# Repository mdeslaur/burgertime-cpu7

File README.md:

# Burgertime CPU-7 module

This is a 1-for-1 reproduction of the Burgertime CPU-7 module which came
encapsulated in epoxy.

The layout and routing is as close to original as possible.

The original board has a wire running from pin 10 of IC3 to a pad on the
lower right corner, and then to the ground plane of the main PCB stack. This
reproduction may work without it, but it is best to add it like on the
original.

Pictures of the original board and a PDF schematic are available in the
docs directory. The gerbers for JLCPCB are in the zip file in the gerbers
directory.

Change history:  
1.0 - Initial version  
1.1 - Updated to add component values, gerbers, and docs.  

To Do:  

Marc Deslauriers  
2022-08-04

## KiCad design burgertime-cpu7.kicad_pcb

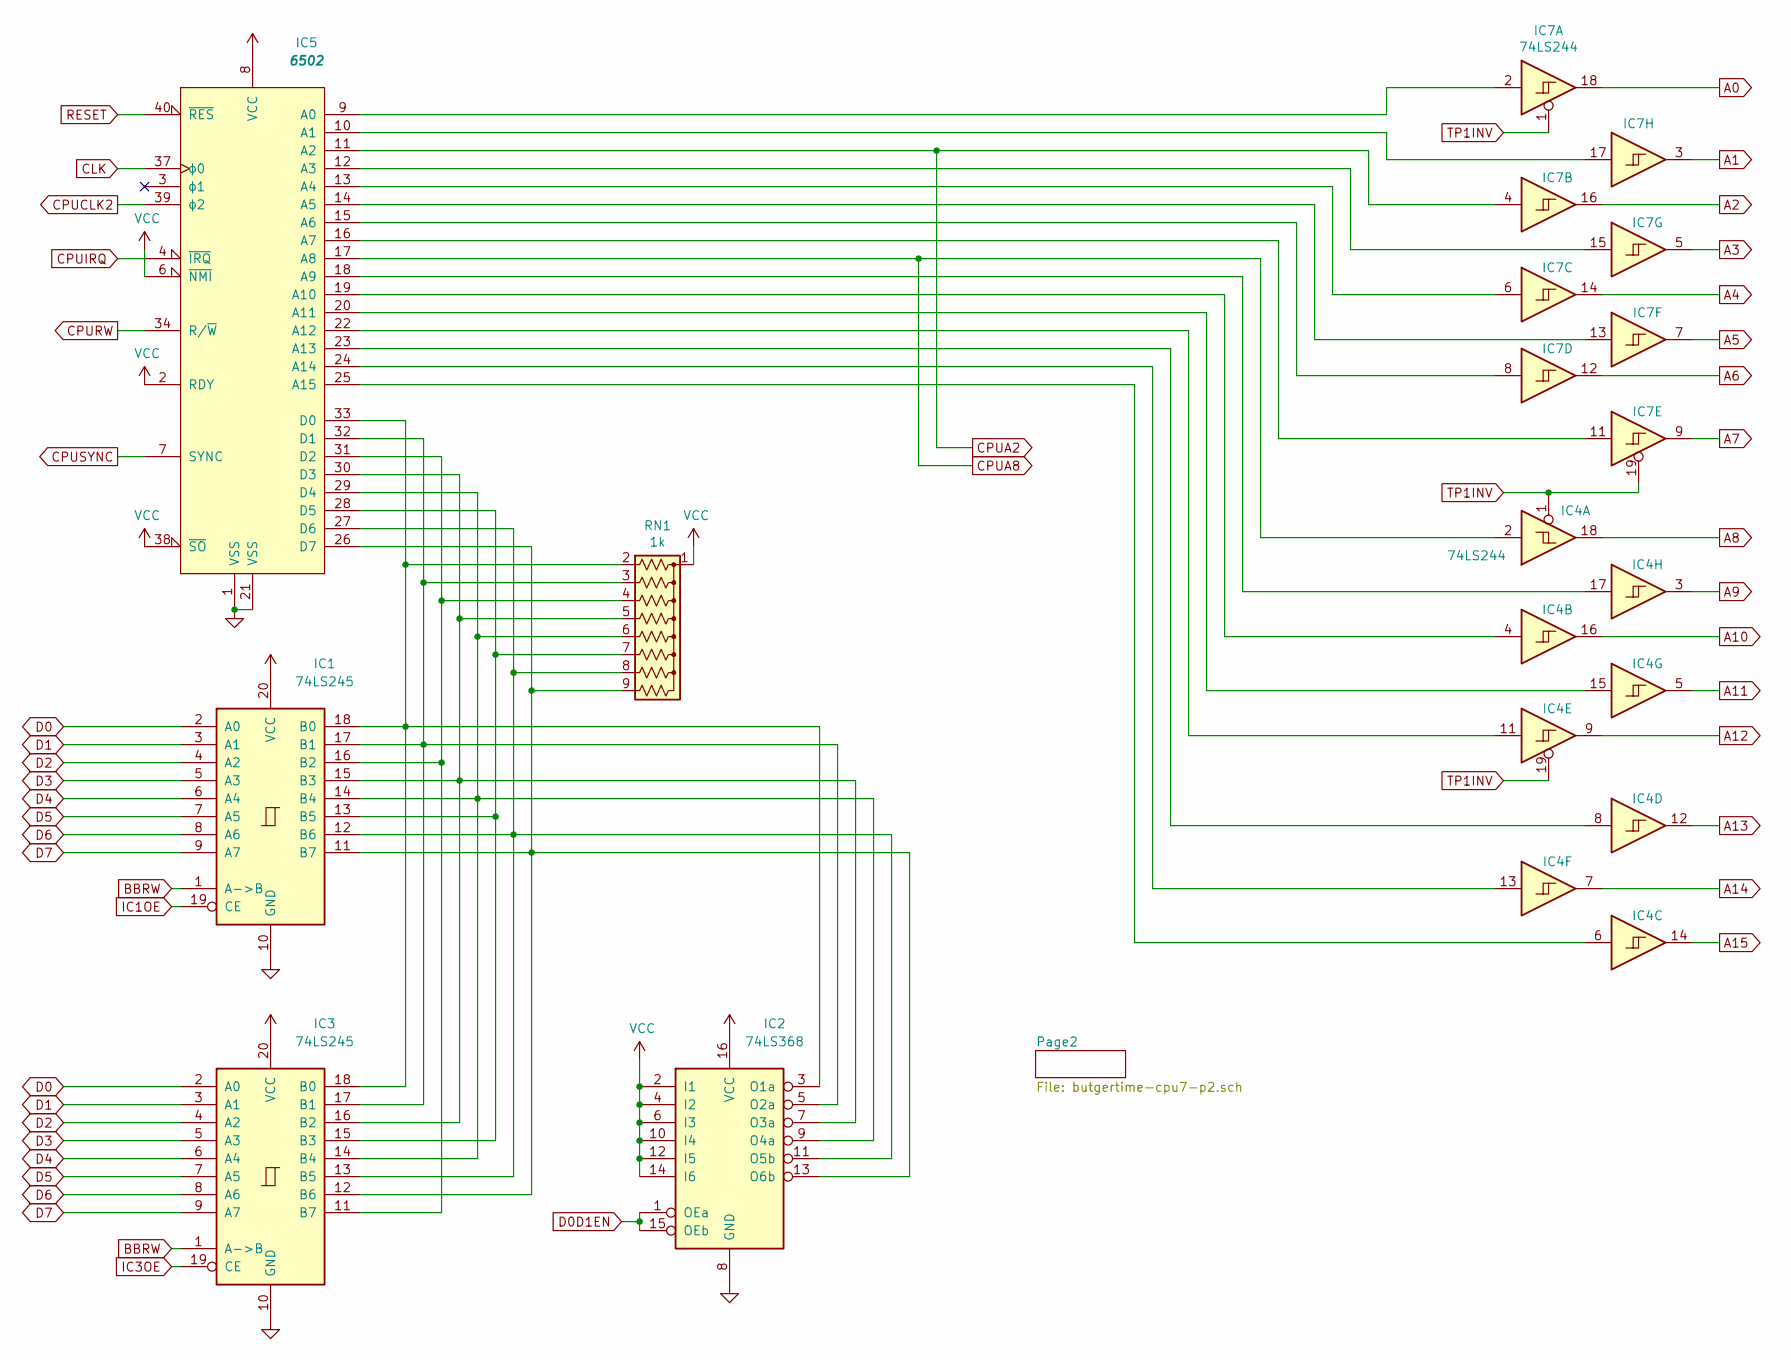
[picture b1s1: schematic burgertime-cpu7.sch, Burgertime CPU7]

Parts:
IC1, IC3: 74LS245; DIP-20_W7.62mm
IC2: 74LS368; DIP-16_W7.62mm
IC4, IC7: 74LS244; DIP-20_W7.62mm
IC5: 6502; DIP-40_W15.24mm
RN1: 1k; R_Array_SIP9

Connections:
A0: IC7.18; also elsewhere on the board
A1: IC7.3; also elsewhere on the board
A2: IC7.16; also elsewhere on the board
A3: IC7.5; also elsewhere on the board
A4: IC7.14; also elsewhere on the board
A5: IC7.7; also elsewhere on the board
A6: IC7.12; also elsewhere on the board
A7: IC7.9; also elsewhere on the board
A8: IC4.18; also elsewhere on the board
A9: IC4.3; also elsewhere on the board
A10: IC4.16; also elsewhere on the board
A11: IC4.5; also elsewhere on the board
A12: IC4.9; also elsewhere on the board
A13: IC4.12; also elsewhere on the board
A14: IC4.7; also elsewhere on the board
A15: IC4.14; also elsewhere on the board
BBRW: IC1.1 (A->B), IC3.1 (A->B); also elsewhere on the board
CLK: IC5.37 (ϕ0); also elsewhere on the board
CPUA2: IC5.11 (A2), IC7.4; also elsewhere on the board
CPUA8: IC4.2, IC5.17 (A8); also elsewhere on the board
CPUCLK2: IC5.39 (ϕ2); also elsewhere on the board
CPUIRQ: IC5.4 (~IRQ); also elsewhere on the board
CPURW: IC5.34 (R/~W); also elsewhere on the board
CPUSYNC: IC5.7 (SYNC); also elsewhere on the board
D0: IC1.2 (A0), IC3.2 (A0); also elsewhere on the board
D0D1EN: IC2.1 (OEa), IC2.15 (OEb); also elsewhere on the board
D1: IC1.3 (A1), IC3.3 (A1); also elsewhere on the board
D2: IC1.4 (A2), IC3.4 (A2); also elsewhere on the board
D3: IC1.5 (A3), IC3.5 (A3); also elsewhere on the board
D4: IC1.6 (A4), IC3.6 (A4); also elsewhere on the board
D5: IC1.7 (A5), IC3.7 (A5); also elsewhere on the board
D6: IC1.8 (A6), IC3.8 (A6); also elsewhere on the board
D7: IC1.9 (A7), IC3.9 (A7); also elsewhere on the board
GND: IC1.10 (GND), IC2.8 (GND), IC3.10 (GND), IC5.1 (VSS), IC5.21 (VSS); also elsewhere on the board
IC1OE: IC1.19 (CE); also elsewhere on the board
IC3OE: IC3.19 (CE); also elsewhere on the board
unnamed: IC1.11 (B7), IC2.13 (O6b), IC3.12 (B6), IC5.26 (D7), RN1.9 (R8)
unnamed: IC1.12 (B6), IC2.11 (O5b), IC3.13 (B5), IC5.27 (D6), RN1.8 (R7)
unnamed: IC1.13 (B5), IC3.15 (B3), IC5.28 (D5), RN1.7 (R6)
unnamed: IC1.14 (B4), IC2.9 (O4a), IC3.14 (B4), IC5.29 (D4), RN1.6 (R5)
unnamed: IC1.15 (B3), IC2.7 (O3a), IC3.16 (B2), IC5.30 (D3), RN1.5 (R4)
unnamed: IC1.16 (B2), IC3.11 (B7), IC5.31 (D2), RN1.4 (R3)
unnamed: IC1.17 (B1), IC2.5 (O2a), IC3.17 (B1), IC5.32 (D1), RN1.3 (R2)
unnamed: IC1.18 (B0), IC2.3 (O1a), IC3.18 (B0), IC5.33 (D0), RN1.2 (R1)
unnamed: IC4.4, IC5.19 (A10)
unnamed: IC4.6, IC5.25 (A15)
unnamed: IC4.8, IC5.23 (A13)
unnamed: IC4.11, IC5.22 (A12)
unnamed: IC4.13, IC5.24 (A14)
unnamed: IC4.15, IC5.20 (A11)
unnamed: IC4.17, IC5.18 (A9)
unnamed: IC5.9 (A0), IC7.2
unnamed: IC5.10 (A1), IC7.17
unnamed: IC5.12 (A3), IC7.15
unnamed: IC5.13 (A4), IC7.6
unnamed: IC5.14 (A5), IC7.13
unnamed: IC5.15 (A6), IC7.8
unnamed: IC5.16 (A7), IC7.11
RESET: IC5.40 (~RES); also elsewhere on the board
TP1INV: IC4.1, IC4.19, IC7.1, IC7.19; also elsewhere on the board
VCC: IC1.20 (VCC), IC2.2 (I1), IC2.4 (I2), IC2.6 (I3), IC2.10 (I4), IC2.12 (I5), IC2.14 (I6), IC2.16 (VCC), IC3.20 (VCC), IC5.2 (RDY), IC5.6 (~NMI), IC5.8 (VCC), IC5.38 (~SO), RN1.1 (common); also elsewhere on the board

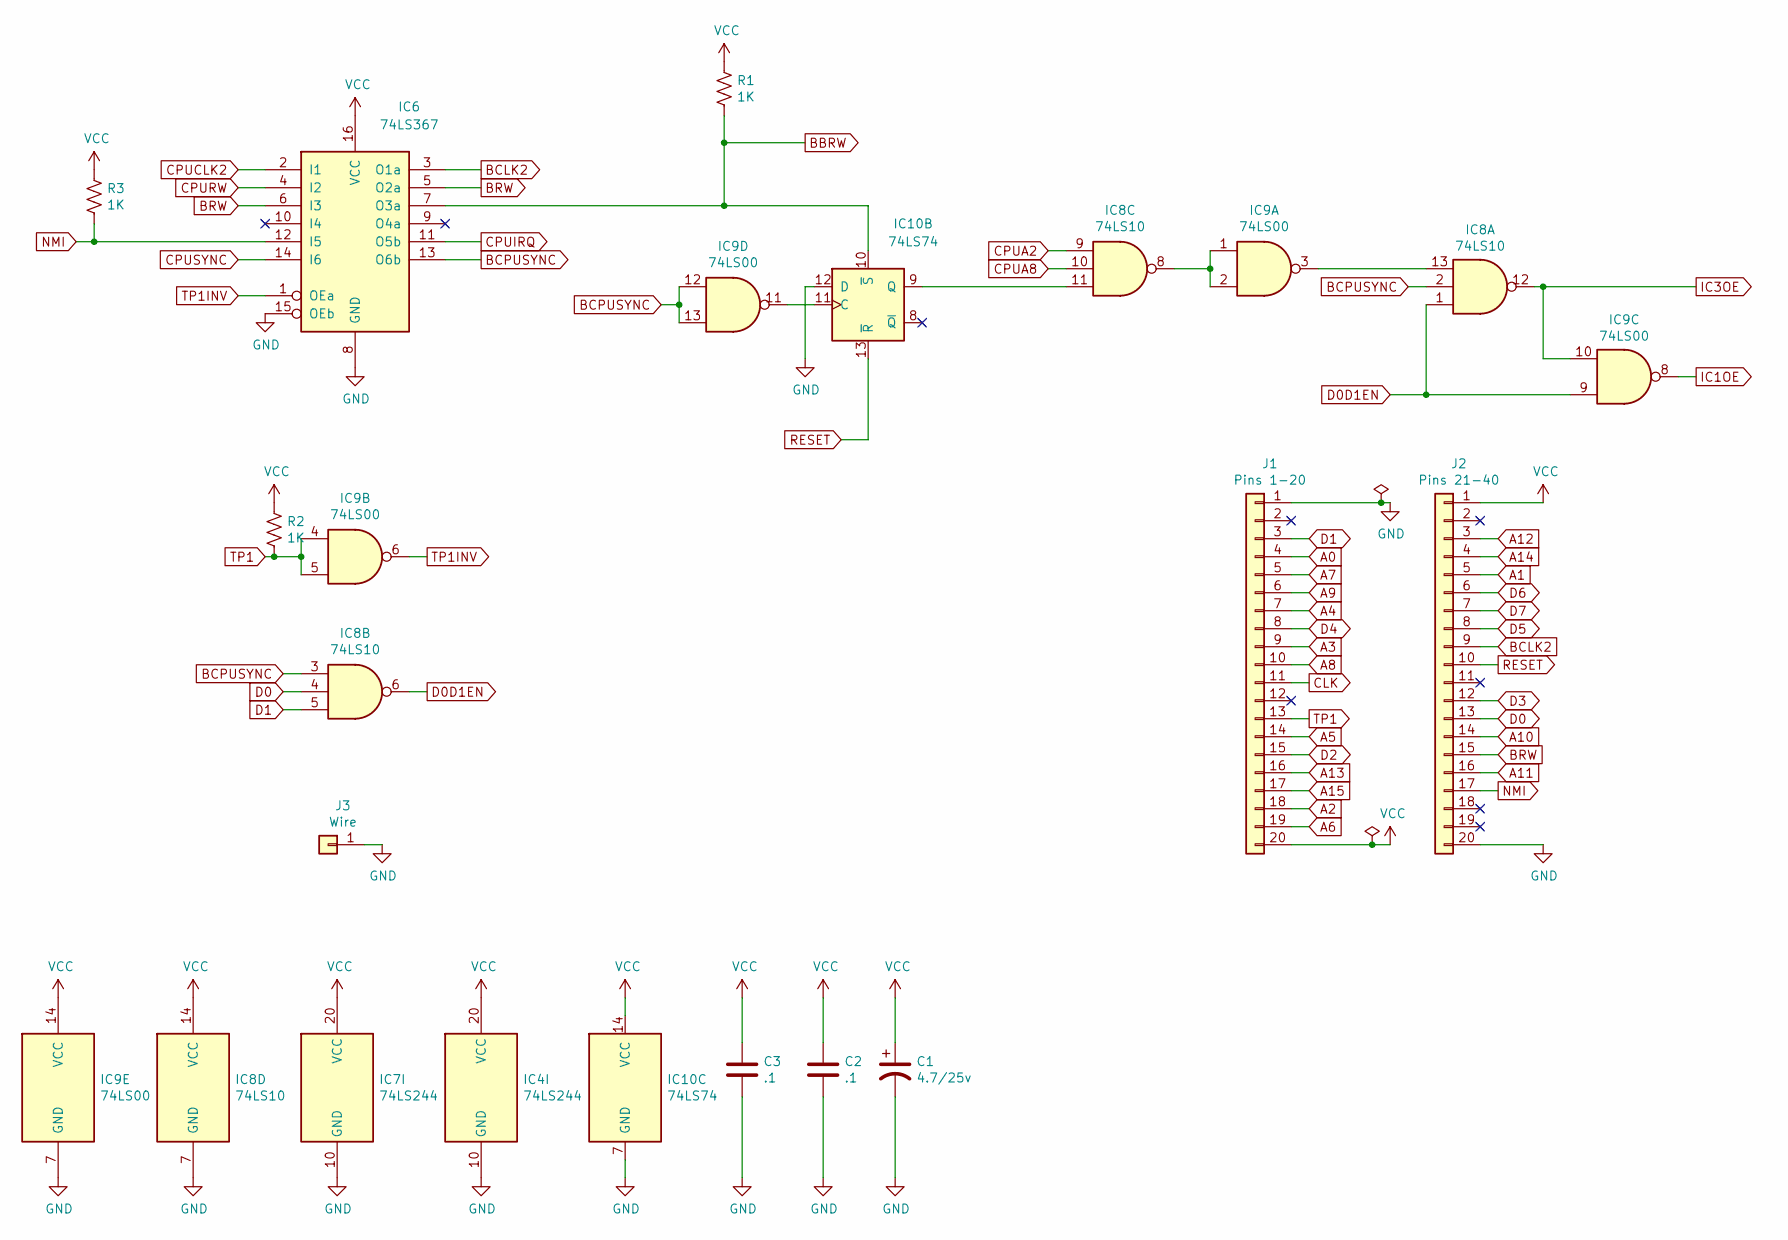
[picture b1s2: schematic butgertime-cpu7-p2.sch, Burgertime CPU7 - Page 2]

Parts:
C1: 4.7/25v; CP_Radial_Tantal_D5.0mm_P5.00mm
C2, C3: .1; C_Disc_D5.0mm_W2.5mm_P5.00mm
IC4, IC7: 74LS244; DIP-20_W7.62mm
IC6: 74LS367; DIP-16_W7.62mm
IC8: 74LS10; DIP-14_W7.62mm
IC9: 74LS00; DIP-14_W7.62mm
IC10: 74LS74; DIP-14_W7.62mm
J1: Pins 1-20; PinHeader_1x20_P2.54mm_Vertical
J2: Pins 21-40; PinHeader_1x20_P2.54mm_Vertical
J3: Wire; SolderWire-0.5sqmm_1x01_D0.9mm_OD2.1mm
R1, R2, R3: 1K; R_Axial_DIN0309_L9.0mm_D3.2mm_P12.70mm_Horizontal

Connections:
A0: J1.4; also elsewhere on the board
A1: J2.5; also elsewhere on the board
A2: J1.18; also elsewhere on the board
A3: J1.9; also elsewhere on the board
A4: J1.7; also elsewhere on the board
A5: J1.14; also elsewhere on the board
A6: J1.19; also elsewhere on the board
A7: J1.5; also elsewhere on the board
A8: J1.10; also elsewhere on the board
A9: J1.6; also elsewhere on the board
A10: J2.14; also elsewhere on the board
A11: J2.16; also elsewhere on the board
A12: J2.3; also elsewhere on the board
A13: J1.16; also elsewhere on the board
A14: J2.4; also elsewhere on the board
A15: J1.17; also elsewhere on the board
BBRW: IC6.7 (O3a), IC10.10 (~S), R1.2; also elsewhere on the board
BCLK2: IC6.3 (O1a), J2.9
BCPUSYNC: IC6.13 (O6b), IC8.2, IC8.3, IC9.12, IC9.13
BRW: IC6.5 (O2a), IC6.6 (I3), J2.15
CLK: J1.11; also elsewhere on the board
CPUA2: IC8.9; also elsewhere on the board
CPUA8: IC8.10; also elsewhere on the board
CPUCLK2: IC6.2 (I1); also elsewhere on the board
CPUIRQ: IC6.11 (O5b); also elsewhere on the board
CPURW: IC6.4 (I2); also elsewhere on the board
CPUSYNC: IC6.14 (I6); also elsewhere on the board
D0: IC8.4, J2.13; also elsewhere on the board
D0D1EN: IC8.1, IC8.6, IC9.9; also elsewhere on the board
D1: IC8.5, J1.3; also elsewhere on the board
D2: J1.15; also elsewhere on the board
D3: J2.12; also elsewhere on the board
D4: J1.8; also elsewhere on the board
D5: J2.8; also elsewhere on the board
D6: J2.6; also elsewhere on the board
D7: J2.7; also elsewhere on the board
GND: C1.2, C2.2, C3.2, IC4.10 (GND), IC6.8 (GND), IC6.15 (OEb), IC7.10 (GND), IC8.7 (GND), IC9.7 (GND), IC10.7 (GND), IC10.12 (D), J1.1, J2.20, J3.1; also elsewhere on the board
IC1OE: IC9.8; also elsewhere on the board
IC3OE: IC8.12, IC9.10; also elsewhere on the board
NMI: IC6.12 (I5), J2.17, R3.2
unnamed: IC8.8, IC9.1, IC9.2
unnamed: IC8.13, IC9.3
unnamed: IC8.11, IC10.9 (Q)
unnamed: IC9.11, IC10.11 (C)
RESET: IC10.13 (~R), J2.10; also elsewhere on the board
TP1: IC9.4, IC9.5, J1.13, R2.2
TP1INV: IC6.1 (OEa), IC9.6; also elsewhere on the board
VCC: C1.1, C2.1, C3.1, IC4.20 (VCC), IC6.16 (VCC), IC7.20 (VCC), IC8.14 (VCC), IC9.14 (VCC), IC10.14 (VCC), J1.20, J2.1, R1.1, R2.1, R3.1; also elsewhere on the board

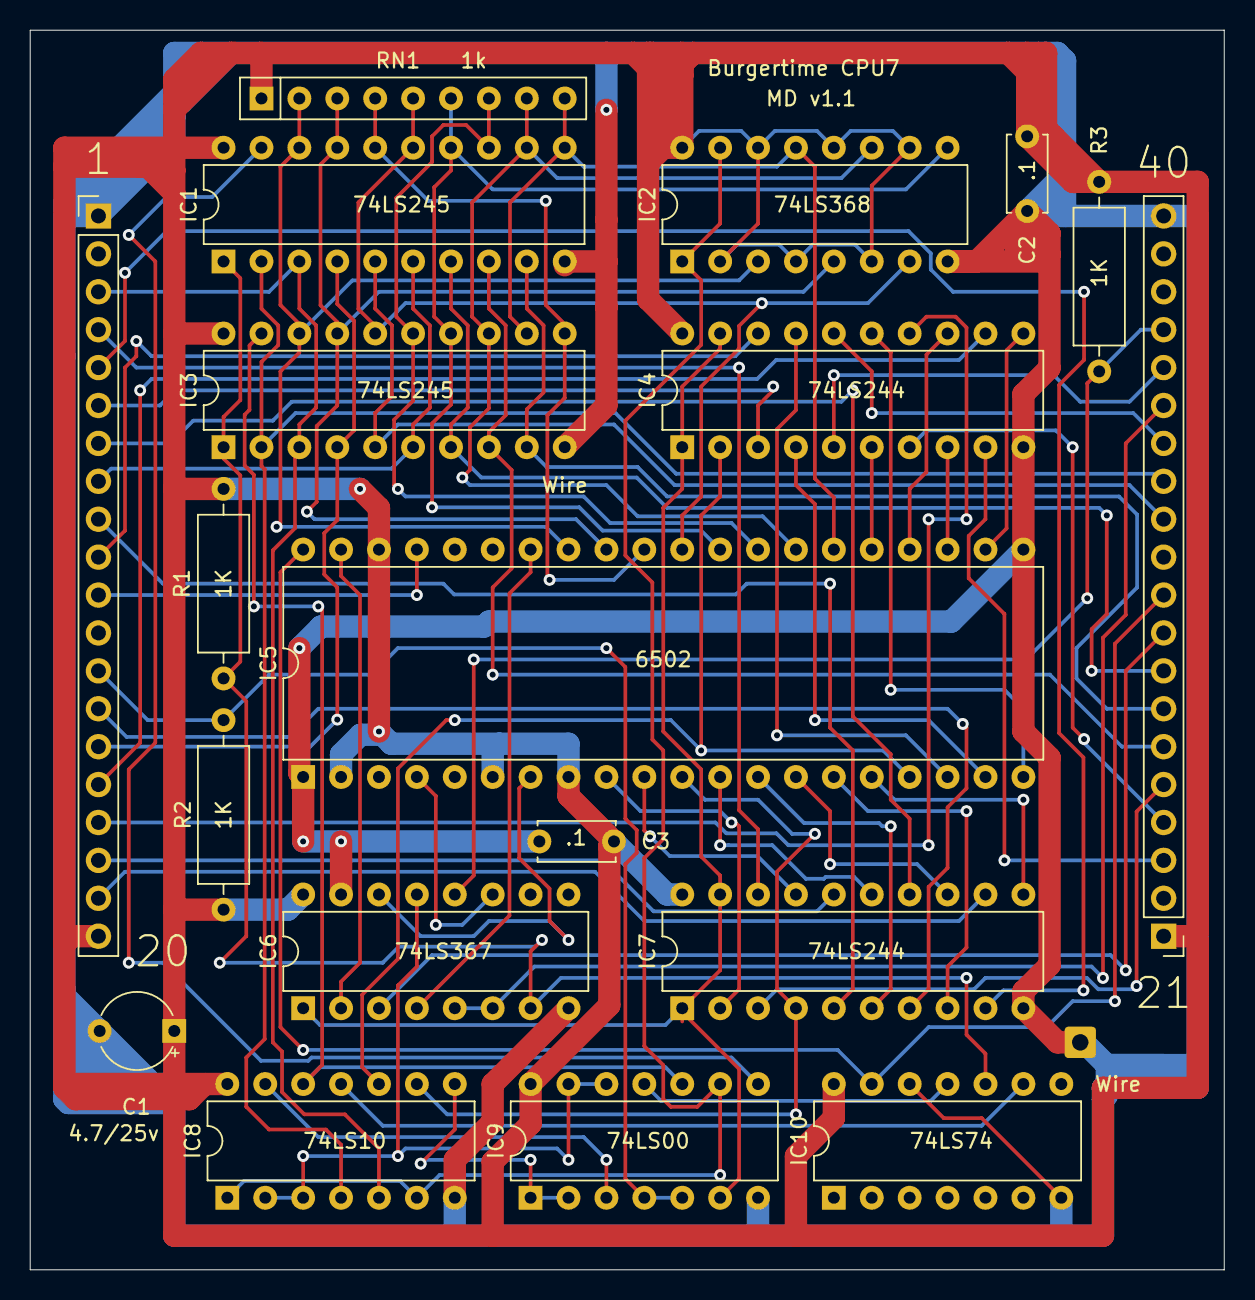
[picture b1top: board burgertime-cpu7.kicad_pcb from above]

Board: 2 copper layers, 80.0 x 83.1 mm, 20 parts (0 on the bottom side), 70 nets.

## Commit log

2022-08-04 added docs, gerbers, and component values to silkscreen
2022-08-04 README.md: correct small mistake
